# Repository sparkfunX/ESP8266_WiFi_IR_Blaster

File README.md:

# ESP8266_WiFi_IR_Blaster
IR blaster based around the ESP8266 ESP12S module.

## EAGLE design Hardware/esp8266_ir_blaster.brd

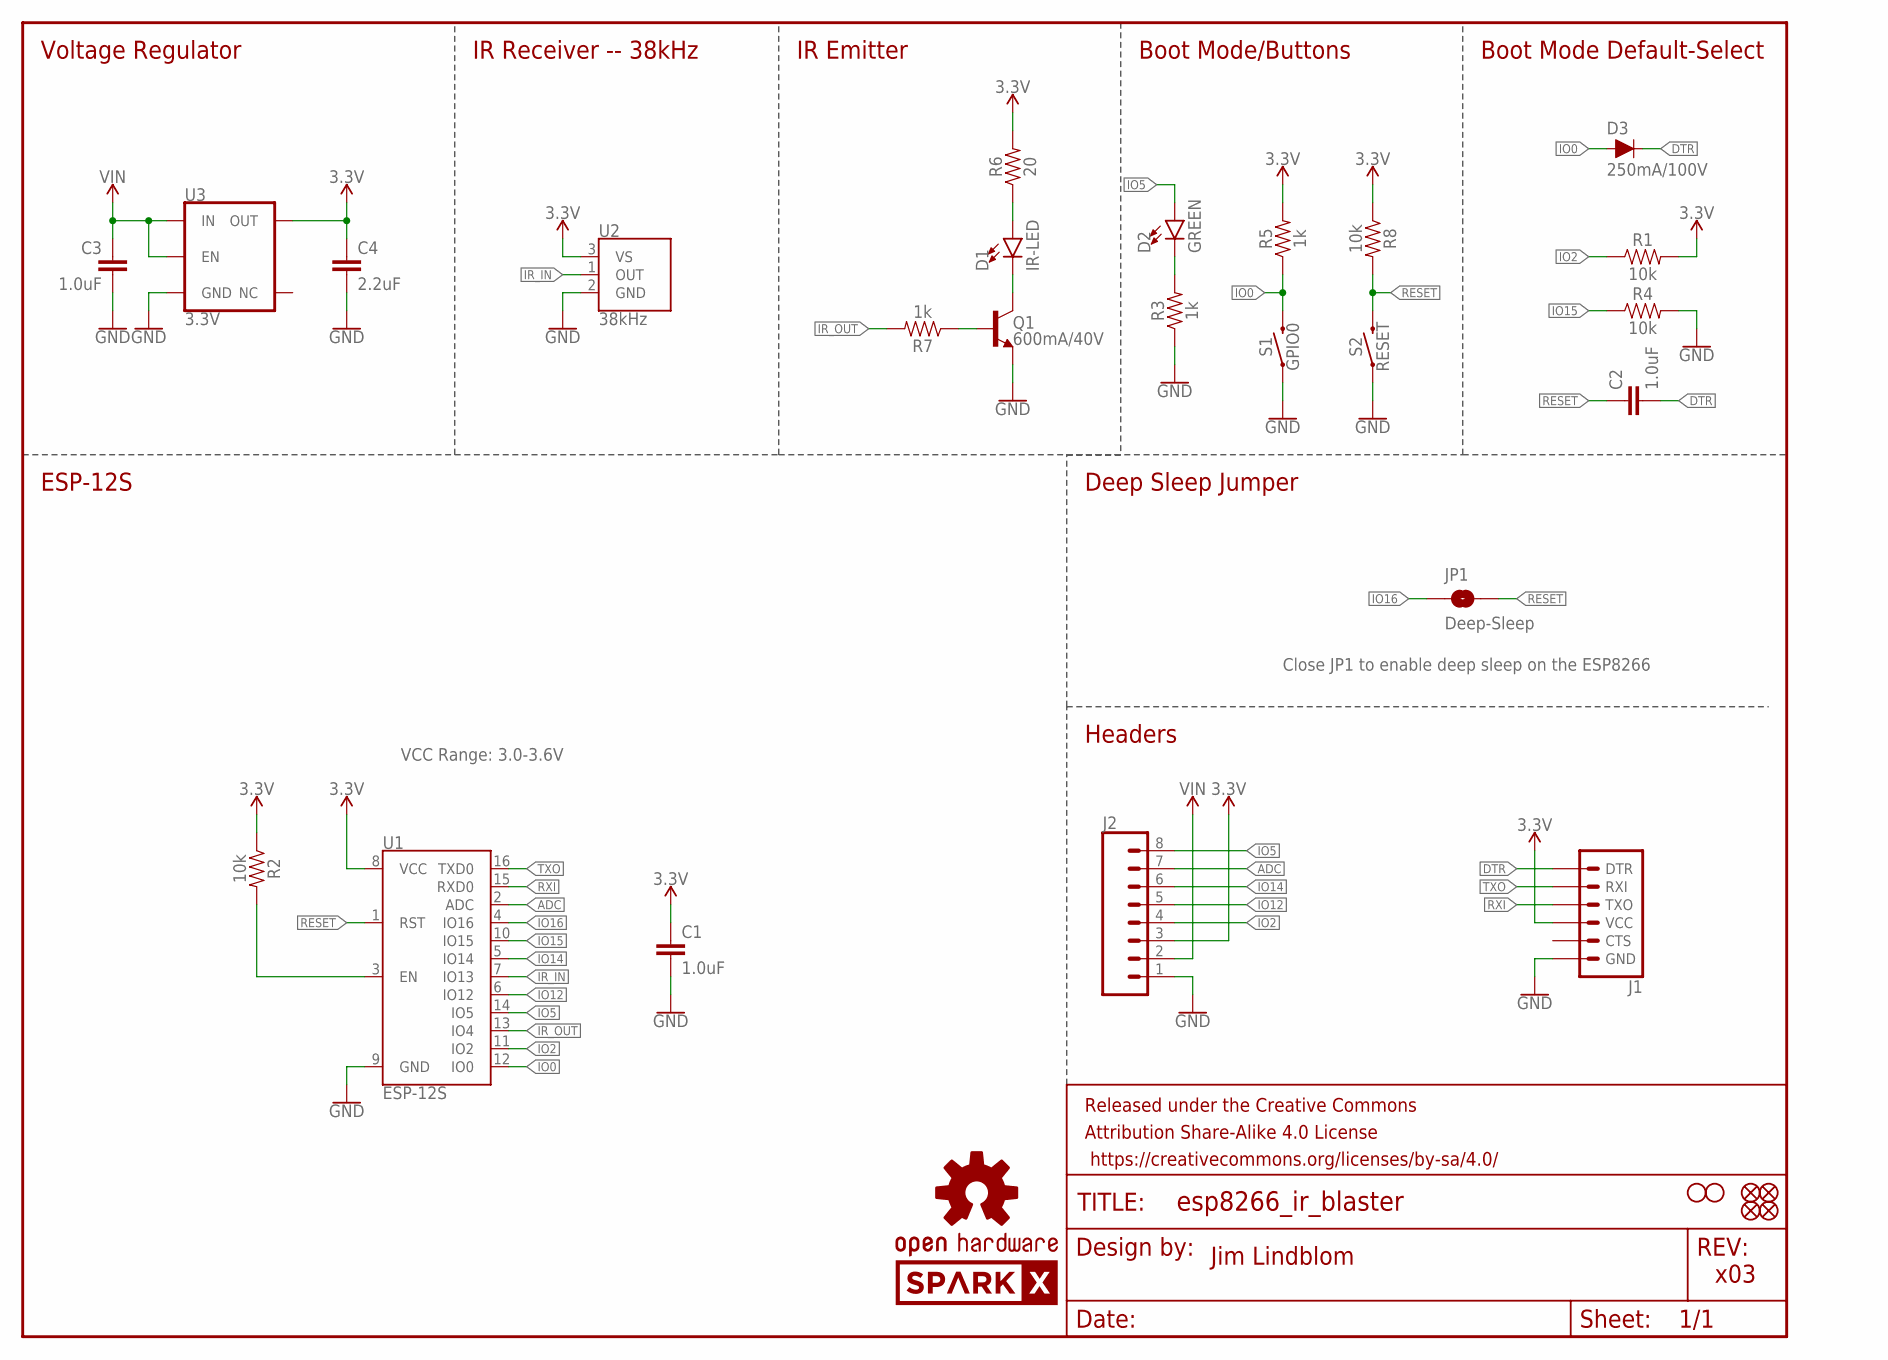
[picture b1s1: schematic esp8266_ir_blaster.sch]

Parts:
C1, C2, C3: 1.0uF; 0603
C4: 2.2uF; 0603
D1: IR-LED; LTE-302
D2: GREEN; LED-0603
D3: 250mA/100V; SOD-323
FD1, FD2, FD3, FD4: FIDUCIALUFIDUCIAL; FIDUCIAL-MICRO
FRAME1: FRAME-LETTER; CREATIVE_COMMONS
H1, H2: STAND-OFF
J1: 6_PIN_SERIAL_TARGETNO_SILK; 1X06_NO_SILK
J2: CONN_08NO_SILK_FEMALE_PTH; 1X08_NO_SILK
JP1: Deep-Sleep; SMT-JUMPER_2_NO_NO-SILK
LOGO1: OSHW-LOGOS; OSHW-LOGO-S
LOGO2: SPARKX-LOGO5; SPARKX-LARGE
Q1: 600mA/40V; SOT23-3
R1, R2, R4, R8: 10k; 0603
R3, R5, R7: 1k; 0603
R6: 20; 0603
S1: GPIO0; TACTILE_SWITCH_SMD_4.6X2.8MM
S2: RESET; TACTILE_SWITCH_SMD_4.6X2.8MM
U1: ESP-12S
U2: 38kHz; TSOP382
U3: 3.3V; SOT23-5

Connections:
3.3V: C1.1, C4.1, J1.4 (VCC), J2.3, R1.2, R2.1, R5.2, R6.2, R8.1, U1.8 (VCC), U2.3 (VS), U3.5 (OUT)
ADC: J2.7, U1.2 (ADC)
CHIP_EN: R2.2, U1.3 (EN)
DTR: C2.2, D3.C, J1.1 (DTR)
GND: C1.2, C3.2, C4.2, J1.6 (GND), J2.1, Q1.2 (E), R3.1, R4.2, S1.1, S1.2 (1), S2.1, S2.2 (1), U1.9 (GND), U2.2 (GND), U3.2 (GND)
IO0: D3.A, R5.1, S1.3 (2), S1.4 (2), U1.12 (IO0)
IO2: J2.4, R1.1, U1.11 (IO2)
IO5: D2.A, J2.8, U1.14 (IO5)
IO12: J2.5, U1.6 (IO12)
IO14: J2.6, U1.5 (IO14)
IO15: R4.1, U1.10 (IO15)
IO16: JP1.1, U1.4 (IO16)
IR_IN: U1.7 (IO13), U2.1 (OUT)
IR_OUT: R7.2, U1.13 (IO4)
unnamed: D2.C, R3.2
unnamed: D1.C, Q1.3 (C)
unnamed: D1.A, R6.1
unnamed: Q1.1 (B), R7.1
RESET: C2.1, JP1.2, R8.2, S2.3 (2), S2.4 (2), U1.1 (RST)
RXI: J1.3 (TXO), U1.15 (RXD0)
TXO: J1.2 (RXI), U1.16 (TXD0)
VIN: C3.1, J2.2, U3.1 (IN), U3.3 (EN)

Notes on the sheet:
Jim Lindblom
x03
IR Receiver -- 38kHz
IR Emitter
Boot Mode/Buttons
Boot Mode Default-Select
Deep Sleep Jumper
Headers
ESP-12S
Close JP1 to enable deep sleep on the ESP8266
VCC Range: 3.0-3.6V
Voltage Regulator

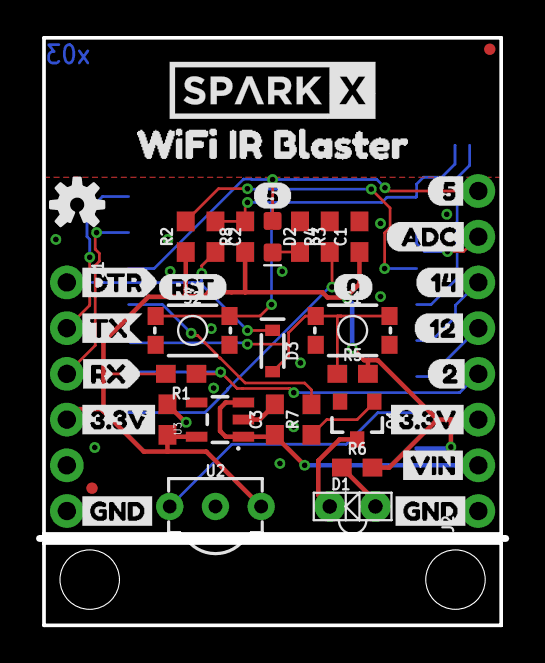
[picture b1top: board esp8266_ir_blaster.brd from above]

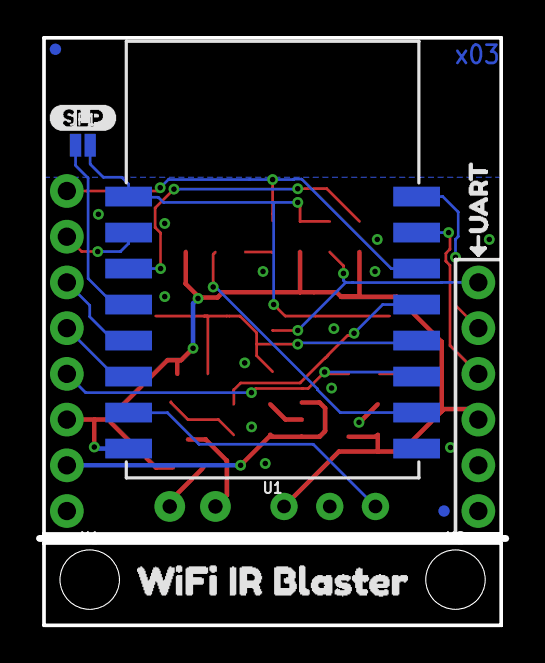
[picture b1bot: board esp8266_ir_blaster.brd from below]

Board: 2 copper layers, 25.9 x 32.5 mm, 53 parts (9 on the bottom side), 22 nets.

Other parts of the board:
U$1: 512
U$2, U$21: 3#3V4
U$3: SLP14
U$4, U$13: WIFI_IR_BLASTER11
U$5: UART0
U$6: DTR1
U$8: 511
U$9: ADC10
U$10: 129
U$11: 148
U$12: 27
U$14: 013
U$15: RST14
U$19: TX2
U$20: RX3
U$22, U$24: GND5
U$23: VIN6

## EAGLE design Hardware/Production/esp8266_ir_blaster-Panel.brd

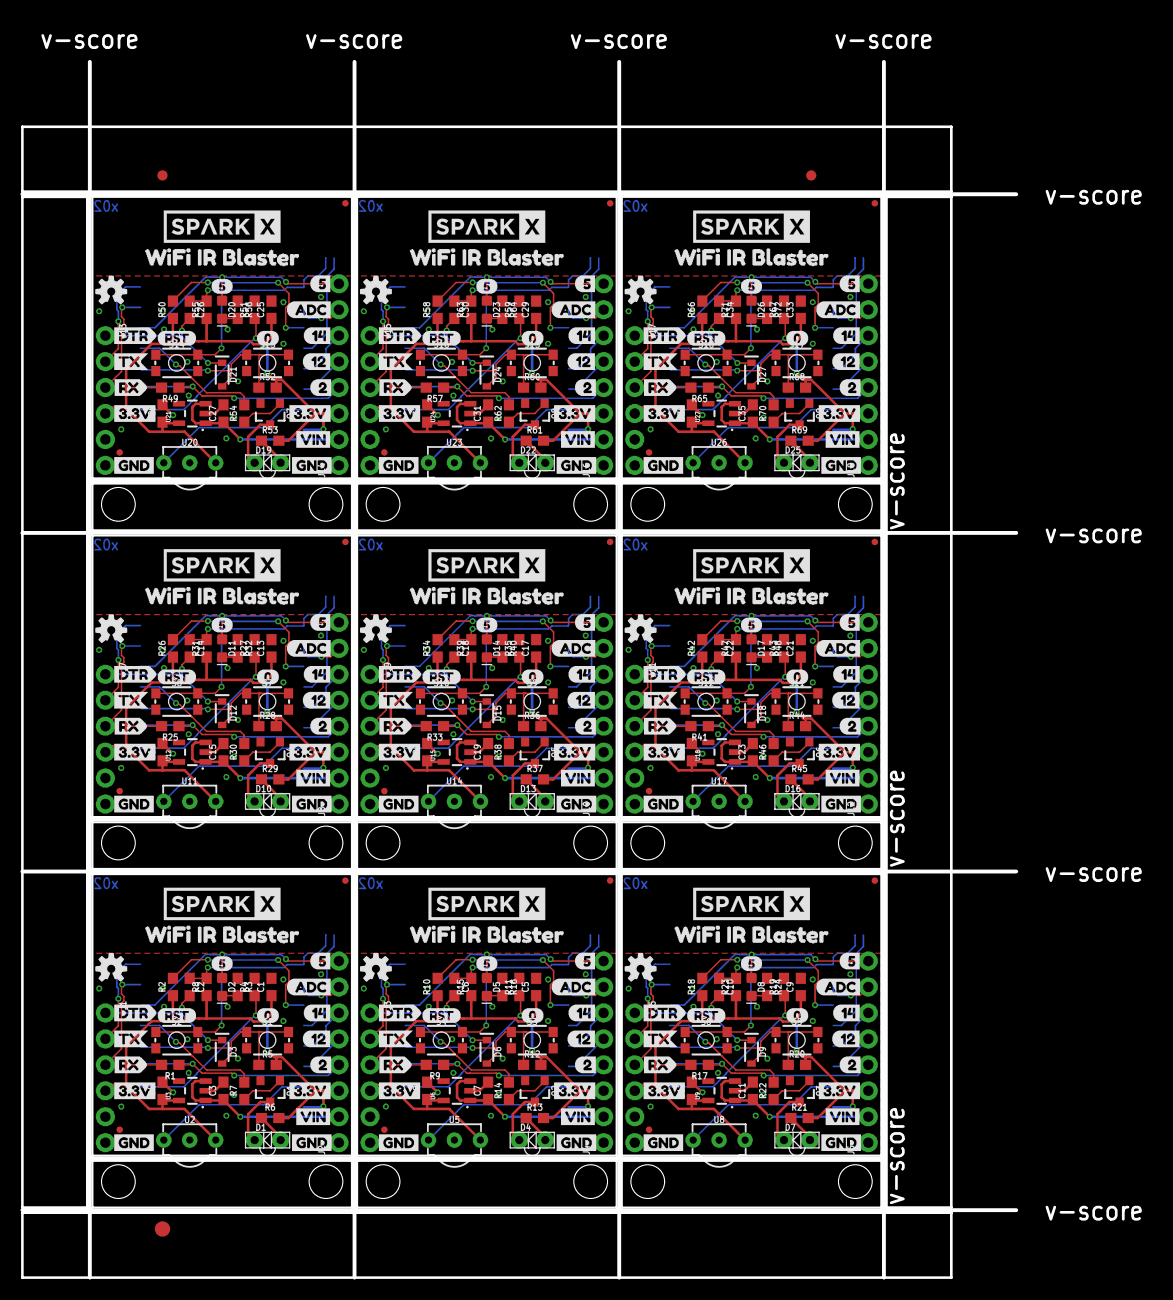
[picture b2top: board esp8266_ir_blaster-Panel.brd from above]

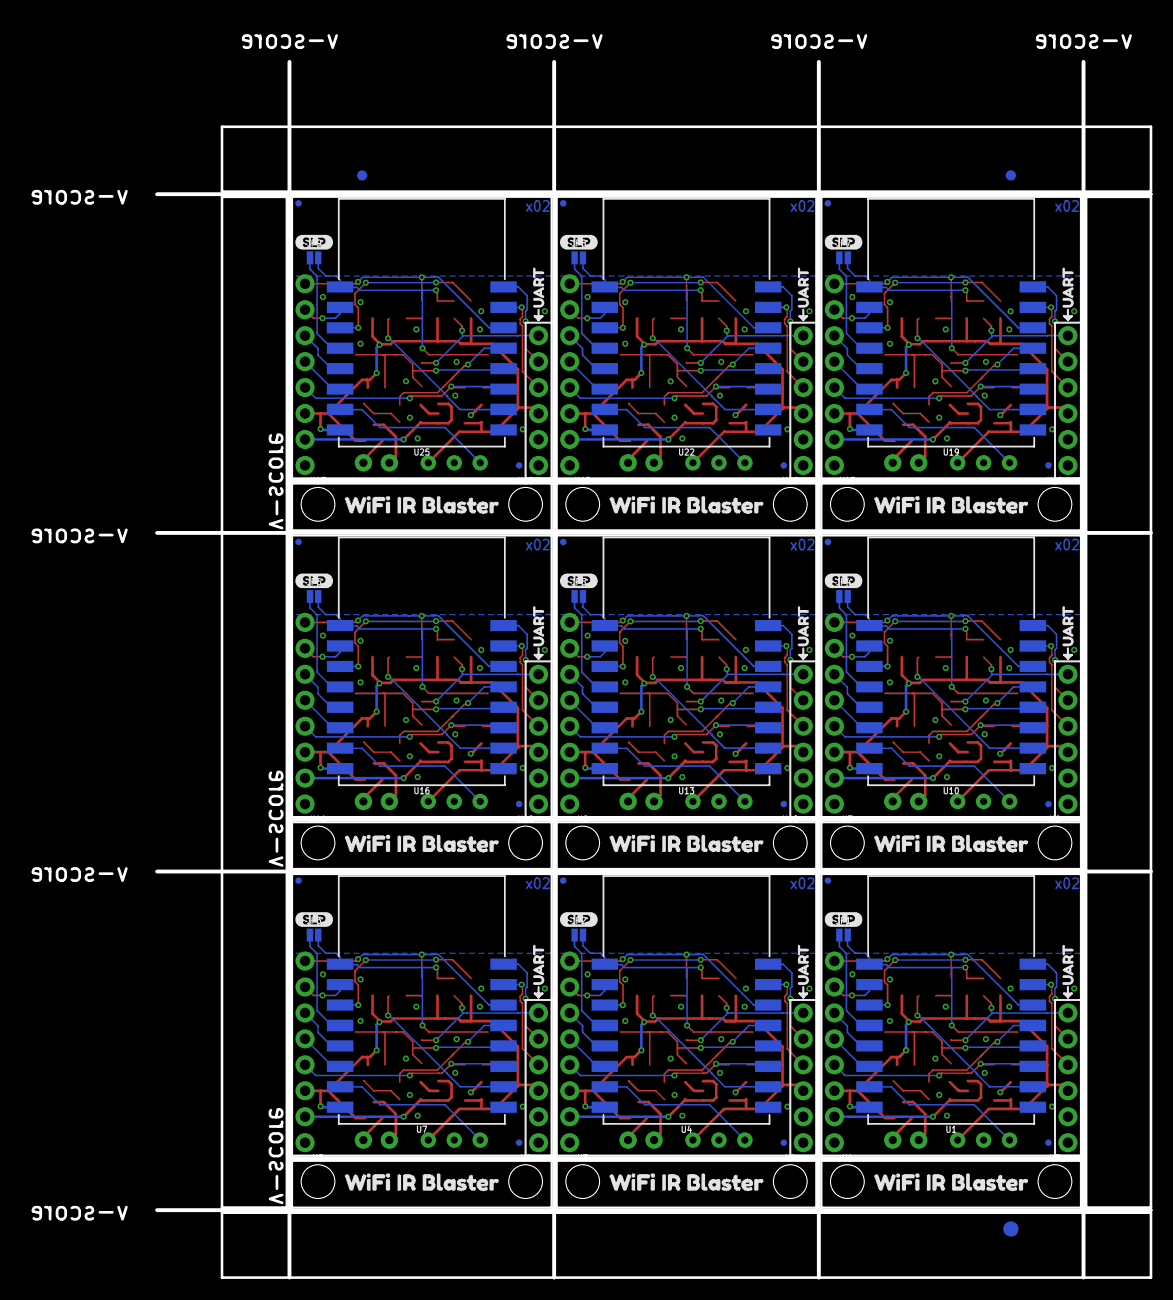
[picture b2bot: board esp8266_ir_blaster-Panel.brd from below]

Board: 2 copper layers, 110.5 x 122.9 mm, 474 parts (84 on the bottom side), 198 nets.

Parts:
C1, C2, C3, C5, C6, C7, C9, C10, C11, C13, C14, C15, C17, C18, C19, C21, C22, C23, C25, C26, C27, C29, C30, C31, C33, C34, C35: 1.0uF; 0603
C4, C8, C12, C16, C20, C24, C28, C32, C36: 2.2uF; 0603
D1, D4, D7, D10, D13, D16, D19, D22, D25: IR-LED; LTE-302
D2, D5, D8, D11, D14, D17, D20, D23, D26: GREEN; LED-0603
D3, D6, D9, D12, D15, D18, D21, D24, D27: 250mA/100V; SOD-323
E$1, E$2, E$3, E$4: FIDUCIAL-1X2
E$5, E$6: FIDUCIAL-1.5X3
FD1, FD2, FD3, FD4, FD5, FD6, FD7, FD8, FD9, FD10, FD11, FD12, FD13, FD14, FD15, FD16, FD17, FD18, FD19, FD20, FD21, FD22, FD23, FD24, FD25, FD26, FD27, FD28, FD29, FD30, FD31, FD32, FD33, FD34, FD35, FD36: FIDUCIALUFIDUCIAL; FIDUCIAL-MICRO
H1, H2, H3, H4, H5, H6, H7, H8, H9, H10, H11, H12, H13, H14, H15, H16, H17, H18: STAND-OFF
J1, J3, J5, J7, J9, J11, J13, J15, J17: 1X06_NO_SILK
J2, J4, J6, J8, J10, J12, J14, J16, J18: 1X08_NO_SILK
JP1, JP2, JP3, JP4, JP5, JP6, JP7, JP8, JP9: Deep-Sleep; SMT-JUMPER_2_NO_NO-SILK
LOGO1, LOGO4, LOGO6, LOGO8, LOGO10, LOGO12, LOGO14, LOGO16, LOGO18: OSHW-LOGOS; OSHW-LOGO-S
LOGO2, LOGO3, LOGO5, LOGO7, LOGO9, LOGO11, LOGO13, LOGO15, LOGO17: SPARKX-LOGO5; SPARKX-LARGE
Q1, Q2, Q3, Q4, Q5, Q6, Q7, Q8, Q9: 600mA/40V; SOT23-3
R1, R2, R4, R8, R9, R10, R11, R15, R17, R18, R19, R23, R25, R26, R27, R31, R33, R34, R35, R39, R41, R42, R43, R47, R49, R50, R51, R55, R57, R58, R59, R63, R65, R66, R67, R71: 10k; 0603
R3, R5, R7, R12, R14, R16, R20, R22, R24, R28, R30, R32, R36, R38, R40, R44, R46, R48, R52, R54, R56, R60, R62, R64, R68, R70, R72: 1k; 0603
R6, R13, R21, R29, R37, R45, R53, R61, R69: 20; 0603
S1, S3, S5, S7, S9, S11, S13, S15, S17: GPIO0; TACTILE_SWITCH_SMD_4.6X2.8MM
S2, S4, S6, S8, S10, S12, S14, S16, S18: RESET; TACTILE_SWITCH_SMD_4.6X2.8MM
U1, U4, U7, U10, U13, U16, U19, U22, U25: ESP-12S
U2, U5, U8, U11, U14, U17, U20, U23, U26: 38kHz; TSOP382
U3, U6, U9, U12, U15, U18, U21, U24, U27: 3.3V; SOT23-5
U$1, U$36, U$56, U$76, U$96, U$116, U$136, U$156, U$176: 512
U$2, U$21, U$27, U$37, U$47, U$57, U$67, U$77, U$87, U$97, U$107, U$117, U$127, U$137, U$147, U$157, U$167, U$177: 3#3V4
U$3, U$38, U$58, U$78, U$98, U$118, U$138, U$158, U$178: SLP14
U$4, U$7, U$13, U$39, U$41, U$59, U$61, U$79, U$81, U$99, U$101, U$119, U$121, U$139, U$141, U$159, U$161, U$179: WIFI_IR_BLASTER11
U$5, U$40, U$60, U$80, U$100, U$120, U$140, U$160, U$180: UART0
U$6, U$18, U$44, U$64, U$84, U$104, U$124, U$144, U$164: DTR1
U$8, U$29, U$49, U$69, U$89, U$109, U$129, U$149, U$169: 511
U$9, U$30, U$50, U$70, U$90, U$110, U$130, U$150, U$170: ADC10
U$10, U$31, U$51, U$71, U$91, U$111, U$131, U$151, U$171: 129
U$11, U$32, U$52, U$72, U$92, U$112, U$132, U$152, U$172: 148
U$12, U$33, U$53, U$73, U$93, U$113, U$133, U$153, U$173: 27
U$14, U$16, U$42, U$62, U$82, U$102, U$122, U$142, U$162: 013
U$15, U$17, U$43, U$63, U$83, U$103, U$123, U$143, U$163: RST14
U$19, U$25, U$45, U$65, U$85, U$105, U$125, U$145, U$165: TX2
U$20, U$26, U$46, U$66, U$86, U$106, U$126, U$146, U$166: RX3
U$22, U$24, U$28, U$35, U$48, U$55, U$68, U$75, U$88, U$95, U$108, U$115, U$128, U$135, U$148, U$155, U$168, U$175: GND5
U$23, U$34, U$54, U$74, U$94, U$114, U$134, U$154, U$174: VIN6

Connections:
3.3V: C1.1, C4.1, J1.4, J2.3, R1.2, R2.1, R5.2, R6.2, R8.1, U1.8, U2.3, U3.5
3.3V1: C5.1, C8.1, J3.4, J4.3, R9.2, R10.1, R12.2, R13.2, R15.1, U4.8, U5.3, U6.5
3.3V2: C9.1, C12.1, J5.4, J6.3, R17.2, R18.1, R20.2, R21.2, R23.1, U7.8, U8.3, U9.5
3.3V3: C13.1, C16.1, J7.4, J8.3, R25.2, R26.1, R28.2, R29.2, R31.1, U10.8, U11.3, U12.5
3.3V4: C17.1, C20.1, J9.4, J10.3, R33.2, R34.1, R36.2, R37.2, R39.1, U13.8, U14.3, U15.5
3.3V5: C21.1, C24.1, J11.4, J12.3, R41.2, R42.1, R44.2, R45.2, R47.1, U16.8, U17.3, U18.5
3.3V6: C25.1, C28.1, J13.4, J14.3, R49.2, R50.1, R52.2, R53.2, R55.1, U19.8, U20.3, U21.5
3.3V7: C29.1, C32.1, J15.4, J16.3, R57.2, R58.1, R60.2, R61.2, R63.1, U22.8, U23.3, U24.5
3.3V8: C33.1, C36.1, J17.4, J18.3, R65.2, R66.1, R68.2, R69.2, R71.1, U25.8, U26.3, U27.5
ADC: J2.7, U1.2
ADC1: J4.7, U4.2
ADC2: J6.7, U7.2
ADC3: J8.7, U10.2
ADC4: J10.7, U13.2
ADC5: J12.7, U16.2
ADC6: J14.7, U19.2
ADC7: J16.7, U22.2
ADC8: J18.7, U25.2
CHIP_EN: R2.2, U1.3
CHIP_EN1: R10.2, U4.3
CHIP_EN2: R18.2, U7.3
CHIP_EN3: R26.2, U10.3
CHIP_EN4: R34.2, U13.3
CHIP_EN5: R42.2, U16.3
CHIP_EN6: R50.2, U19.3
CHIP_EN7: R58.2, U22.3
CHIP_EN8: R66.2, U25.3
DTR: C2.2, D3.C, J1.1
DTR1: C6.2, D6.C, J3.1
DTR2: C10.2, D9.C, J5.1
DTR3: C14.2, D12.C, J7.1
DTR4: C18.2, D15.C, J9.1
DTR5: C22.2, D18.C, J11.1
DTR6: C26.2, D21.C, J13.1
DTR7: C30.2, D24.C, J15.1
DTR8: C34.2, D27.C, J17.1
GND: C1.2, C3.2, C4.2, J1.6, J2.1, Q1.2, R3.1, R4.2, S1.1, S1.2, S2.1, S2.2, U1.9, U2.2, U3.2
GND1: C5.2, C7.2, C8.2, J3.6, J4.1, Q2.2, R11.2, R16.1, S3.1, S3.2, S4.1, S4.2, U4.9, U5.2, U6.2
GND2: C9.2, C11.2, C12.2, J5.6, J6.1, Q3.2, R19.2, R24.1, S5.1, S5.2, S6.1, S6.2, U7.9, U8.2, U9.2
GND3: C13.2, C15.2, C16.2, J7.6, J8.1, Q4.2, R27.2, R32.1, S7.1, S7.2, S8.1, S8.2, U10.9, U11.2, U12.2
GND4: C17.2, C19.2, C20.2, J9.6, J10.1, Q5.2, R35.2, R40.1, S9.1, S9.2, S10.1, S10.2, U13.9, U14.2, U15.2
GND5: C21.2, C23.2, C24.2, J11.6, J12.1, Q6.2, R43.2, R48.1, S11.1, S11.2, S12.1, S12.2, U16.9, U17.2, U18.2
GND6: C25.2, C27.2, C28.2, J13.6, J14.1, Q7.2, R51.2, R56.1, S13.1, S13.2, S14.1, S14.2, U19.9, U20.2, U21.2
GND7: C29.2, C31.2, C32.2, J15.6, J16.1, Q8.2, R59.2, R64.1, S15.1, S15.2, S16.1, S16.2, U22.9, U23.2, U24.2
GND8: C33.2, C35.2, C36.2, J17.6, J18.1, Q9.2, R67.2, R72.1, S17.1, S17.2, S18.1, S18.2, U25.9, U26.2, U27.2
IO0: D3.A, R5.1, S1.3, S1.4, U1.12
IO1: R11.1, U4.10
IO2: J2.4, R1.1, U1.11
IO3: J4.4, R9.1, U4.11
IO4: D6.A, R12.1, S3.3, S3.4, U4.12
IO5: D2.A, J2.8, U1.14
IO6: J4.6, U4.5
IO7: JP2.1, U4.4
IO8: J4.5, U4.6
IO9: D5.A, J4.8, U4.14
IO10: R19.1, U7.10
IO11: J6.4, R17.1, U7.11
IO12: J2.5, U1.6
IO13: D9.A, R20.1, S5.3, S5.4, U7.12
IO14: J2.6, U1.5
IO15: R4.1, U1.10
IO16: JP1.1, U1.4
IO17: J6.6, U7.5
IO18: JP3.1, U7.4
IO19: J6.5, U7.6
IO20: D8.A, J6.8, U7.14
IO21: R27.1, U10.10
IO22: J8.4, R25.1, U10.11
IO23: D12.A, R28.1, S7.3, S7.4, U10.12
IO24: J8.6, U10.5
IO25: JP4.1, U10.4
IO26: J8.5, U10.6
IO27: D11.A, J8.8, U10.14
IO28: R35.1, U13.10
IO29: J10.4, R33.1, U13.11
IO30: D15.A, R36.1, S9.3, S9.4, U13.12
IO31: J10.6, U13.5
IO32: JP5.1, U13.4
IO33: J10.5, U13.6
IO34: D14.A, J10.8, U13.14
IO35: R43.1, U16.10
IO36: J12.4, R41.1, U16.11
IO37: D18.A, R44.1, S11.3, S11.4, U16.12
IO38: J12.6, U16.5
IO39: JP6.1, U16.4
IO40: J12.5, U16.6
IO41: D17.A, J12.8, U16.14
IO42: R51.1, U19.10
IO43: J14.4, R49.1, U19.11
IO44: D21.A, R52.1, S13.3, S13.4, U19.12
IO45: J14.6, U19.5
IO46: JP7.1, U19.4
IO47: J14.5, U19.6
IO48: D20.A, J14.8, U19.14
IO49: R59.1, U22.10
IO50: J16.4, R57.1, U22.11
IO51: D24.A, R60.1, S15.3, S15.4, U22.12
IO52: J16.6, U22.5
IO53: JP8.1, U22.4
IO54: J16.5, U22.6
IO55: D23.A, J16.8, U22.14
IO56: R67.1, U25.10
IO57: J18.4, R65.1, U25.11
IO58: D27.A, R68.1, S17.3, S17.4, U25.12
IO59: J18.6, U25.5
IO60: JP9.1, U25.4
IO61: J18.5, U25.6
IO62: D26.A, J18.8, U25.14
IR_IN: U1.7, U2.1
IR_IN1: U4.7, U5.1
IR_IN2: U7.7, U8.1
IR_IN3: U10.7, U11.1
IR_IN4: U13.7, U14.1
IR_IN5: U16.7, U17.1
IR_IN6: U19.7, U20.1
IR_IN7: U22.7, U23.1
IR_IN8: U25.7, U26.1
IR_OUT: R7.2, U1.13
IR_OUT1: R14.2, U4.13
IR_OUT2: R22.2, U7.13
IR_OUT3: R30.2, U10.13
IR_OUT4: R38.2, U13.13
IR_OUT5: R46.2, U16.13
IR_OUT6: R54.2, U19.13
IR_OUT7: R62.2, U22.13
IR_OUT8: R70.2, U25.13
unnamed: D2.C, R3.2
unnamed: D4.C, Q2.3
unnamed: D4.A, R13.1
unnamed: Q2.1, R14.1
unnamed: D1.C, Q1.3
unnamed: D1.A, R6.1
unnamed: Q1.1, R7.1
unnamed: D5.C, R16.2
unnamed: D7.C, Q3.3
unnamed: D7.A, R21.1
unnamed: Q3.1, R22.1
unnamed: D8.C, R24.2
unnamed: D10.C, Q4.3
unnamed: D10.A, R29.1
unnamed: Q4.1, R30.1
unnamed: D11.C, R32.2
unnamed: D13.C, Q5.3
unnamed: D13.A, R37.1
unnamed: Q5.1, R38.1
unnamed: D14.C, R40.2
unnamed: D16.C, Q6.3
unnamed: D16.A, R45.1
unnamed: Q6.1, R46.1
unnamed: D17.C, R48.2
unnamed: D19.C, Q7.3
unnamed: D19.A, R53.1
unnamed: Q7.1, R54.1
unnamed: D20.C, R56.2
unnamed: D22.C, Q8.3
unnamed: D22.A, R61.1
unnamed: Q8.1, R62.1
unnamed: D23.C, R64.2
unnamed: D25.C, Q9.3
unnamed: D25.A, R69.1
unnamed: Q9.1, R70.1
unnamed: D26.C, R72.2
RESET: C2.1, JP1.2, R8.2, S2.3, S2.4, U1.1
RESET1: C6.1, JP2.2, R15.2, S4.3, S4.4, U4.1
RESET2: C10.1, JP3.2, R23.2, S6.3, S6.4, U7.1
RESET3: C14.1, JP4.2, R31.2, S8.3, S8.4, U10.1
RESET4: C18.1, JP5.2, R39.2, S10.3, S10.4, U13.1
RESET5: C22.1, JP6.2, R47.2, S12.3, S12.4, U16.1
RESET6: C26.1, JP7.2, R55.2, S14.3, S14.4, U19.1
RESET7: C30.1, JP8.2, R63.2, S16.3, S16.4, U22.1
RESET8: C34.1, JP9.2, R71.2, S18.3, S18.4, U25.1
RXI: J1.3, U1.15
RXI1: J3.3, U4.15
RXI2: J5.3, U7.15
RXI3: J7.3, U10.15
RXI4: J9.3, U13.15
RXI5: J11.3, U16.15
RXI6: J13.3, U19.15
RXI7: J15.3, U22.15
RXI8: J17.3, U25.15
TXO: J1.2, U1.16
TXO1: J3.2, U4.16
TXO2: J5.2, U7.16
TXO3: J7.2, U10.16
TXO4: J9.2, U13.16
TXO5: J11.2, U16.16
TXO6: J13.2, U19.16
TXO7: J15.2, U22.16
TXO8: J17.2, U25.16
VIN: C3.1, J2.2, U3.1, U3.3
VIN1: C7.1, J4.2, U6.1, U6.3
VIN2: C11.1, J6.2, U9.1, U9.3
VIN3: C15.1, J8.2, U12.1, U12.3
VIN4: C19.1, J10.2, U15.1, U15.3
VIN5: C23.1, J12.2, U18.1, U18.3
VIN6: C27.1, J14.2, U21.1, U21.3
VIN7: C31.1, J16.2, U24.1, U24.3
VIN8: C35.1, J18.2, U27.1, U27.3

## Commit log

2018-06-19 initial commit of hardware
2018-06-19 x01 panel
2018-07-18 Revising LED color. Adding production panel.
2018-08-07 x02 hardware commit
2018-09-18 Adding ESP12-S and IR datasheets.
2018-09-18 Adding x02 schematic.
2018-09-19 Adding content to readme
2018-09-25 Increasing drill size for IR receiver holes.
2018-09-27 Adding test firmware and simple batch file.

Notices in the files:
parts and their libraries:
SparkFun-Aesthetics: Licensing: Creative Commons ShareAlike 4.0 International - https://creativecommons.org/licenses/by-sa/4.0
SparkFun-Aesthetics: Released under the Creative Commons Attribution Share-Alike 4.0 License
SparkFun-Aesthetics: https://creativecommons.org/licenses/by-sa/4.0
